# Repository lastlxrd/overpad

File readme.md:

# OVERPAD

A custom 12-key mechanical macropad with a rotary encoder, OLED display and RGB, powered by QMK.

<sub>[@lastlxrd](https://github.com/lastlxrd) · 2024</sub>

OVERPAD is a compact programmable macropad built around the ATmega32U4 and QMK Firmware.

## Features

- 12 mechanical keys
- Rotary encoder with push button
- ATmega32U4 microcontroller
- 128×64 OLED display
- 12× WS2812 RGB LEDs
- QMK Firmware
- VIA support
- USB HID
- NKRO support
- Mouse keys and media controls
- Caterina bootloader

## Hardware

| Component | Description |
|---|---|
| MCU | ATmega32U4 |
| Keys | 12 mechanical keys |
| Encoder | Rotary encoder with push button |
| Display | 128×64 OLED |
| RGB | 12× WS2812 LEDs |
| Firmware | QMK |
| Configuration | VIA |
| Bootloader | Caterina |

## VIA configuration

OVERPAD supports VIA, allowing the keymap to be customized through a graphical interface without recompiling the firmware.

With VIA you can:

- Remap all 12 keys
- Configure multiple layers
- Assign media and system controls
- Create macros
- Change shortcuts and key functions
- Customize the layout without reflashing the firmware

The VIA definition is included in the repository:

[`keymaps/via/via.json`](keymaps/via/via.json)

### How to customize OVERPAD with VIA

1. Connect OVERPAD to your computer via USB.

2. Open VIA.

3. If OVERPAD is detected automatically, open the **Configure** tab and start remapping the keys.

4. If the keyboard is not detected automatically, enable the **Design** tab in VIA settings.

5. Load:

[`keymaps/via/via.json`](keymaps/via/via.json)

6. Return to the **Configure** tab.

7. Select any key on the OVERPAD layout and assign the desired function.

Changes are written directly to the keyboard and take effect immediately.

> OVERPAD must be running the VIA-enabled QMK firmware for VIA configuration to work.

## Firmware

OVERPAD firmware is based on QMK Firmware.

The repository contains the keyboard configuration files:

```text id="a8ulgl"
.
├── config.h
├── keyboard.json
├── rules.mk
├── LICENSE
├── NOTICE
├── LICENSE-ASSETS.md
├── docs/
│   ├── overpad1.jpg
│   ├── overpad2.jpg
│   └── overpad3.jpg
└── README.md
```

To use the keyboard definition inside a QMK installation, place it in:

```text id="mnyxy5"
qmk_firmware/keyboards/lastlxrd/overpad/
```

A QMK keymap can then be placed inside:

```text id="mnyxy5"
keymaps/default/ 
```

and compiled with:

```bash id="k6jx0a"
qmk compile -kb lastlxrd/overpad -km default
```

or flashed with:

```bash id="hzysyd"
qmk flash -kb lastlxrd/overpad -km default
```

> A `keymaps/default/keymap.c` file is required to build a complete firmware image.

## About

OVERPAD is an early custom hardware project developed in 2024.

The project combines PCB design, embedded firmware and mechanical keyboard hardware in a compact programmable controller.

## License

OVERPAD firmware and keyboard configuration files are licensed under the GNU General Public License v2.0 or later (`GPL-2.0-or-later`).

The firmware is based on QMK Firmware, which is distributed under the GNU General Public License.

Original project photographs and media located in `docs/` are not covered by the firmware license unless explicitly stated otherwise.

See `LICENSE`, `NOTICE` and `LICENSE-ASSETS.md` for details.

## Author

Designed and developed by [lastlxrd](https://github.com/lastlxrd).

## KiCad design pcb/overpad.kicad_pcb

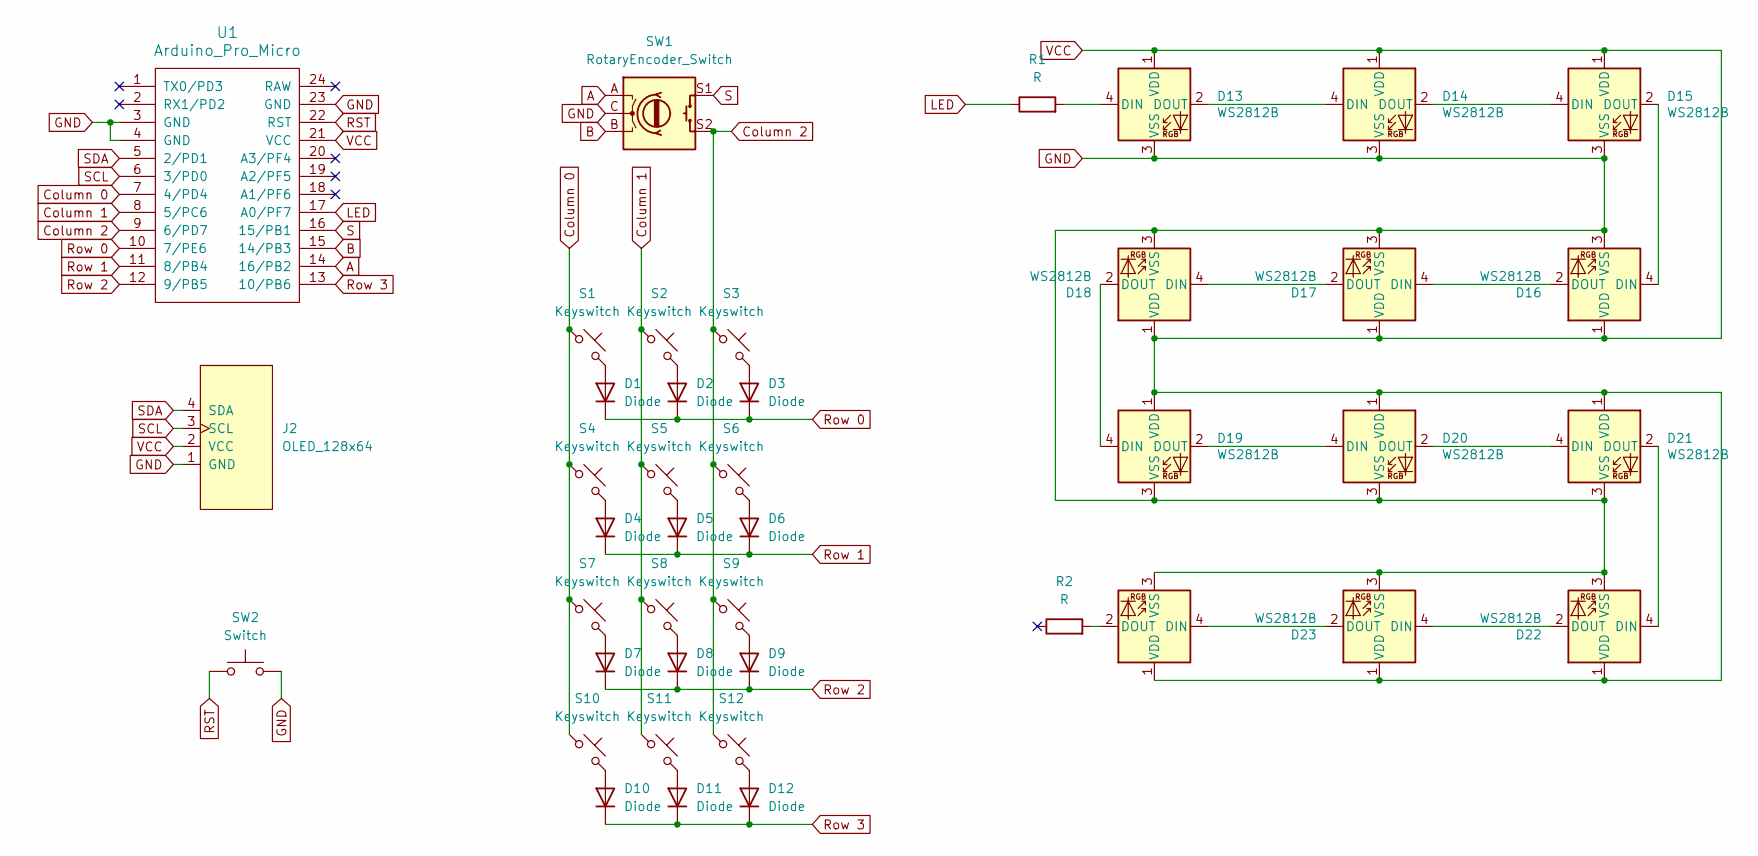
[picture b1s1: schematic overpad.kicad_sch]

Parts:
D1, D2, D3, D4, D5, D6, D7, D8, D9, D10, D11, D12: Diode; Diode_DO-35
D13, D14, D15, D16, D17, D18, D19, D20, D21, D22, D23, D24: WS2812B; LED_WS2812B_PLCC4_5.0x5.0mm_P3.2mm
J2: OLED_128x64
R1, R2: R; R_Axial_DIN0207_L6.3mm_D2.5mm_P7.62mm_Horizontal
S1, S2, S3, S4, S5, S6, S7, S8, S9, S10, S11, S12: Keyswitch; Hotswap_MX_Plated_1.00u
SW1: RotaryEncoder_Switch; Encoder_EC11_MX
SW2: Switch; Button_MJTP1243
U1: Arduino_Pro_Micro

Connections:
A: SW1.A, U1.14 (16/PB2)
B: SW1.B, U1.15 (14/PB3)
Column 0: S1.1, S4.1, S7.1, S10.1, U1.7 (4/PD4)
Column 1: S2.1, S5.1, S8.1, S11.1, U1.8 (5/PC6)
Column 2: S3.1, S6.1, S9.1, S12.1, SW1.S2, U1.9 (6/PD7)
GND: D13.3 (VSS), D14.3 (VSS), D15.3 (VSS), D16.3 (VSS), D17.3 (VSS), D18.3 (VSS), D19.3 (VSS), D20.3 (VSS), D21.3 (VSS), D22.3 (VSS), D23.3 (VSS), D24.3 (VSS), J2.1 (GND), SW1.C, SW2.2, U1.3 (GND), U1.4 (GND), U1.23 (GND)
LED: R1.1, U1.17 (A0/PF7)
unnamed: D1.2 (A), S1.2
unnamed: D2.2 (A), S2.2
unnamed: D3.2 (A), S3.2
unnamed: D4.2 (A), S4.2
unnamed: D5.2 (A), S5.2
unnamed: D6.2 (A), S6.2
unnamed: D7.2 (A), S7.2
unnamed: D8.2 (A), S8.2
unnamed: D9.2 (A), S9.2
unnamed: D10.2 (A), S10.2
unnamed: D11.2 (A), S11.2
unnamed: D12.2 (A), S12.2
unnamed: D13.4 (DIN), R1.2
unnamed: D13.2 (DOUT), D14.4 (DIN)
unnamed: D14.2 (DOUT), D15.4 (DIN)
unnamed: D15.2 (DOUT), D16.4 (DIN)
unnamed: D16.2 (DOUT), D17.4 (DIN)
unnamed: D17.2 (DOUT), D18.4 (DIN)
unnamed: D18.2 (DOUT), D19.4 (DIN)
unnamed: D19.2 (DOUT), D20.4 (DIN)
unnamed: D20.2 (DOUT), D21.4 (DIN)
unnamed: D21.2 (DOUT), D22.4 (DIN)
unnamed: D22.2 (DOUT), D23.4 (DIN)
unnamed: D23.2 (DOUT), D24.4 (DIN)
unnamed: D24.2 (DOUT), R2.2
RST: SW2.1, U1.22 (RST)
Row 0: D1.1 (K), D2.1 (K), D3.1 (K), U1.10 (7/PE6)
Row 1: D4.1 (K), D5.1 (K), D6.1 (K), U1.11 (8/PB4)
Row 2: D7.1 (K), D8.1 (K), D9.1 (K), U1.12 (9/PB5)
Row 3: D10.1 (K), D11.1 (K), D12.1 (K), U1.13 (10/PB6)
S: SW1.S1, U1.16 (15/PB1)
SCL: J2.3 (SCL), U1.6 (3/PD0)
SDA: J2.4 (SDA), U1.5 (2/PD1)
VCC: D13.1 (VDD), D14.1 (VDD), D15.1 (VDD), D16.1 (VDD), D17.1 (VDD), D18.1 (VDD), D19.1 (VDD), D20.1 (VDD), D21.1 (VDD), D22.1 (VDD), D23.1 (VDD), D24.1 (VDD), J2.2 (VCC), U1.21 (VCC)

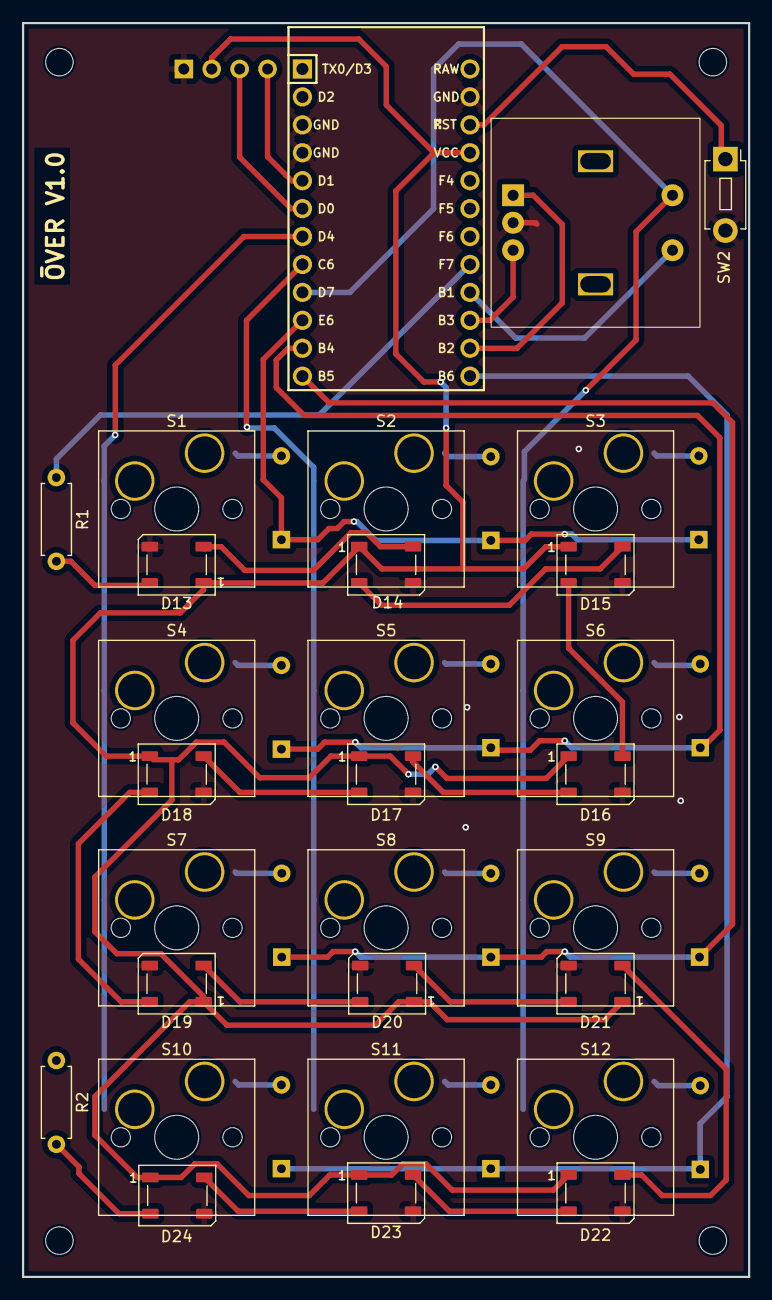
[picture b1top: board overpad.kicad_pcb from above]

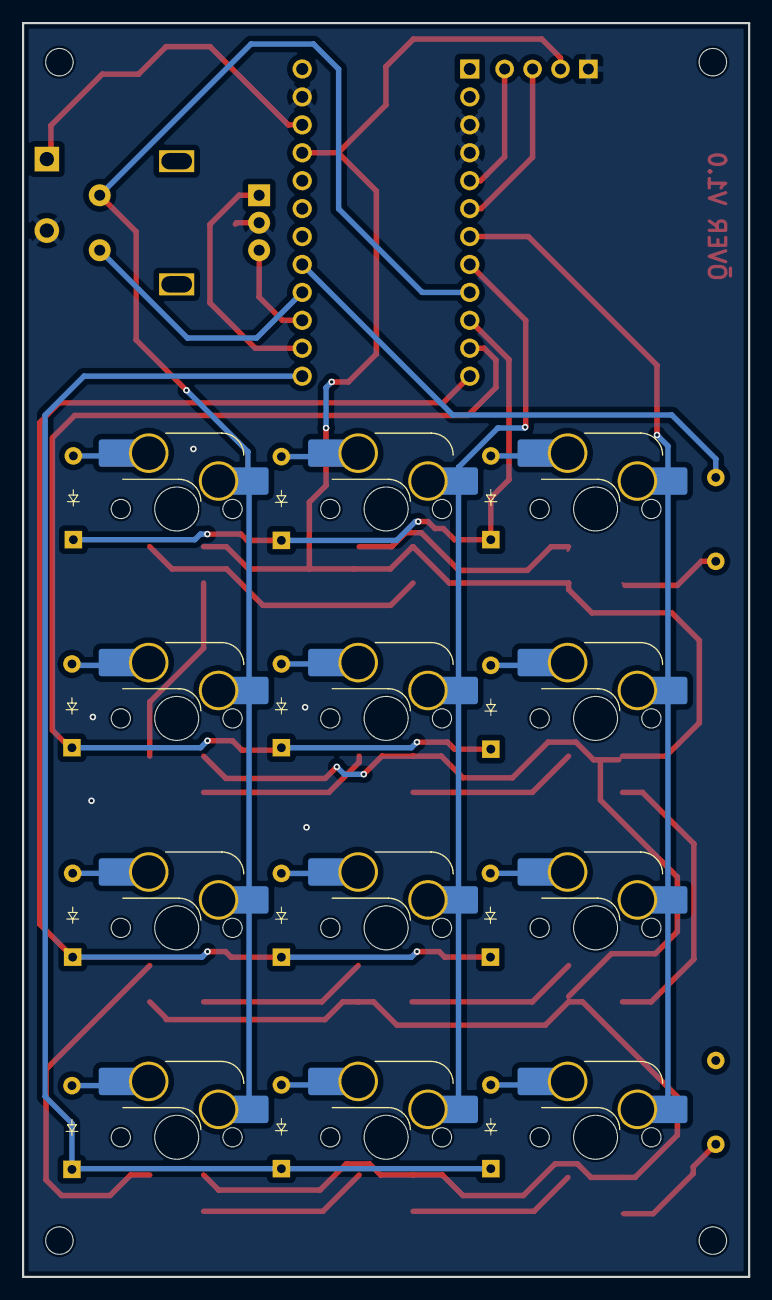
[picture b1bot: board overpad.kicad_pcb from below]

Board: 2 copper layers, 66.0 x 114.0 mm, 42 parts (12 on the bottom side), 41 nets.
